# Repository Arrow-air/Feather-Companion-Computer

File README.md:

# Feather Flight Companion Computer

## Ground Control Station & Onboard Flight UI

### Functions:
1. Data Logger
2. Telemetry Server
3. User Interface Engine

## Table of Contents
1. [Introduction](#introduction)
2. [Architecture Overview](#architecture-overview)
3. [File Descriptions](#file-descriptions)
    - [FCPC.py](#fcpcpy)
    - [Data.py](#datapy)
    - [Veronte.py](#verontepy)
    - [BMS.py](#bmspy)
    - [VESCCAN.py](#vesccanpy)
    - [ESC.py](#escpy)
    - [CyphalCAN3.py](#cyphalcan3py)
    - [TCP.py](#tcppy)
    - [server.py](#serverpy)
    - [protocols_functions.py](#protocols_functionspy)
    - [display1.py](#display1py)
    - [display2.py](#display2py)
    - [Joystick.py](#joystickpy)
    - [LoRa.py](#lorapy)
    - [IO.py](#iopy)

## Introduction

The Flight Companion Computer system designed for both Ground Control Station (GCS) and onboard flight use (FUI). It integrates multiple functionalities including data logging, telemetry server, and a user interface engine. The system is modular, allowing for easy expansion and maintenance, and is designed to provide a robust Data interface for flight operations.

## Architecture Overview

The system is structured into multiple modules, each handling a specific aspect of the overall functionality. These modules include communication protocols, data handling, user interfaces, and specific hardware controls. The main control program loop resides in the `FCPC.py` file.

## File Descriptions

### FCPC.py
**Main Function and Control Logic**  
The central script that coordinates the activities of all other modules. Handles high-level decision making and ensures smooth operation of the entire system.

### Data.py
**Data Handling Module**  
Manages data storage and retrieval within the system. Provides functions for logging data, managing data formats, packaging data to be sent as telemetry.

### Veronte.py
**Veronte Module**  
Interfaces with the main Flight Controller, the Embention Veronte X1, over UART serial. packages flight sensor data, such as attitude and altitude etc.

### BMS.py
**Battery Management System (BMS) Module**  
Packages data from each of the 6 Ennoid X-LITE-V4 BMSs on board the aircraft, including voltage, current, temperature, and state of charge, etc.

### VESCCAN.py
**VESC-CAN Module**  
Interfaces with the VESC CAN bus protocol for interacting with data emminating from the Ennoid X-LITE-V4 BMSs, as implemented by Ennoid.

### ESC.py
**Electronic Speed Controller (ESC) Module**  
Packages data from each of the 6 Mad Motors ECSs on board the aircraft, including voltage, current, temperature, and state of charge, etc.

### CyphalCAN3.py
**Cyphal-CAN Protocol Module**  
Interfaces with the Cyphal-CAN CAN bus protocol for interacting with data emminating from the MAD Motors ECS, as implemented by MAD Motors.

### TCP.py
**TCP/IP Communication Module**  
Implements communication over TCP/IP, handling socket connections, data transmission, and reception over local network, send telemetry data to the displays.

### server.py
**Server Module**  
Sets up a network connection to `display1.py` and `display2.py` to send telementry data to the display screens

### protocols_functions.py
**Protocols Utility Functions Module**  
Contains utility functions used by `server.py`, `display1.py`, and `display2.py`. Provides common functionalities such as message parsing, checksum calculation, and other specific operations.

### display1.py
**Display Module 1**  
Responsible for rendering the "System State Window", primarily displaying data from the Flight Controller.

### display2.py
**Display Module 2**  
Responsible for rendering the "System Infromation Window", primarily displaying data from all the ESCs and BMSs.

### Joystick.py
**Joystick Input Module**  
Handles input from but Logitec USB and Otto CAN joystick devices. Reads joystick movements and button presses, translating their commands to the control system.

### LoRa.py
**Long Range Radio Communication Module**  
Implements communication over the LoRa protocol for long-range, low-power wireless communication. Handles message encoding, decoding, and transmission.

### IO.py
**Input-Output Module**  
Manages I/O on the RPI GPIO pins.

---

This README provides a comprehensive overview of the Project Feather system and its components. For detailed usage and additional information, refer to the documentation within each module and the main `FCPC.py` script, as well as the following reference documents:

## FCPC Concept Document 

[FCPC Concept]( https://docs.google.com/document/d/15r7cTYvV1hOLt8er7vyQtWU0twEOfAIIOQ0pdE-wRtA/edit?pli=1#heading=h.xr0raokzut1w )

## Project Feather Data Network & Ground Equipment Document

[Data Network & Ground Equipment]( https://docs.google.com/document/d/11VlSYsE245VFLZsYB7TvqWuuJ1UnPRjPKnnLWUzqcEM/edit )

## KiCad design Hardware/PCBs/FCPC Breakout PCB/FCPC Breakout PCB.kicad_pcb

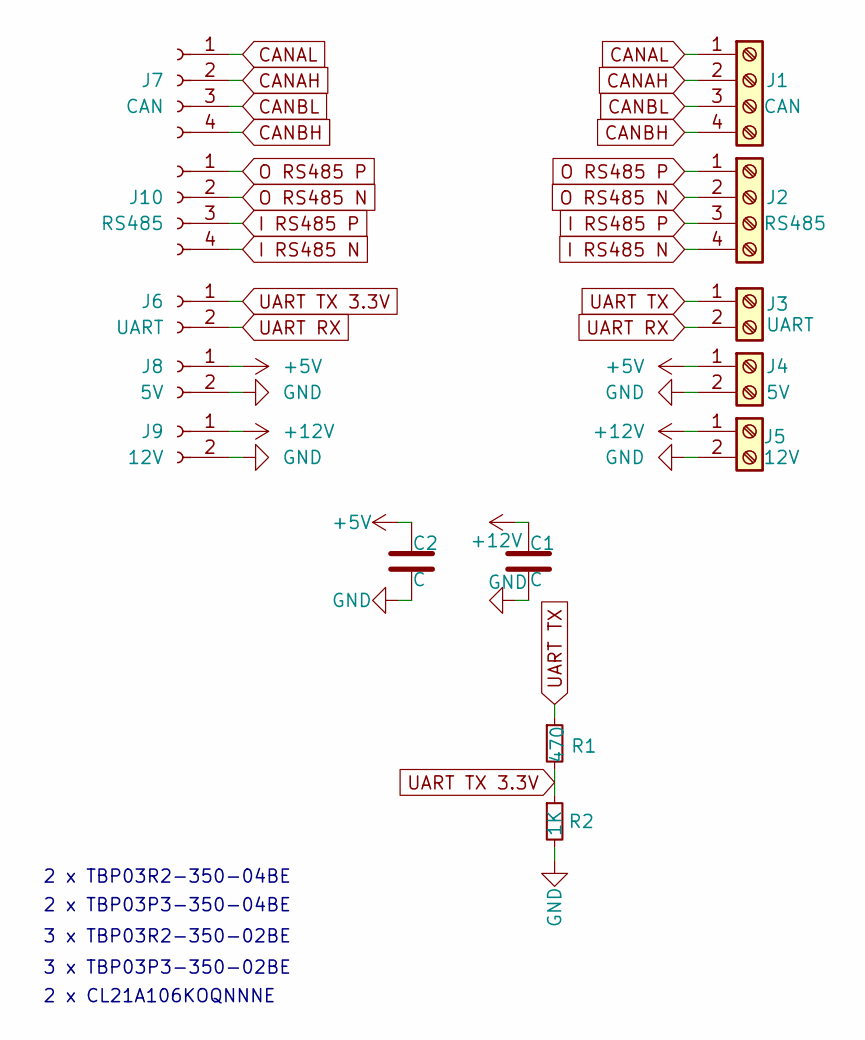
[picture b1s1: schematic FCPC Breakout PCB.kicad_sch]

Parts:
C1, C2: C; C_0805_2012Metric_Pad1.18x1.45mm_HandSolder
J1: CAN; PhoenixContact_MCV_1,5_4-G-3.5_1x04_P3.50mm_Vertical
J2: RS485; PhoenixContact_MCV_1,5_4-G-3.5_1x04_P3.50mm_Vertical
J3: UART; PhoenixContact_MCV_1,5_2-G-3.5_1x02_P3.50mm_Vertical
J4: 5V; PhoenixContact_MCV_1,5_2-G-3.5_1x02_P3.50mm_Vertical
J5: 12V; PhoenixContact_MCV_1,5_2-G-3.5_1x02_P3.50mm_Vertical
J6: UART; PinHeader_1x02_P2.54mm_Vertical
J7: CAN; PinHeader_1x04_P2.54mm_Vertical
J8: 5V; PinHeader_1x02_P2.54mm_Vertical
J9: 12V; PinHeader_1x02_P2.54mm_Vertical
J10: RS485; PinHeader_1x04_P2.54mm_Vertical
R1: 470; R_0805_2012Metric_Pad1.20x1.40mm_HandSolder
R2: 1K; R_0805_2012Metric_Pad1.20x1.40mm_HandSolder

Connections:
+5V: C2.1, J4.1, J8.1
+12V: C1.1, J5.1, J9.1
CANAH: J1.2, J7.2
CANAL: J1.1, J7.1
CANBH: J1.4, J7.4
CANBL: J1.3, J7.3
GND: C1.2, C2.2, J4.2, J5.2, J8.2, J9.2, R2.2
I RS485 N: J2.4, J10.4
I RS485 P: J2.3, J10.3
O RS485 N: J2.2, J10.2
O RS485 P: J2.1, J10.1
UART RX: J3.2, J6.2
UART TX: J3.1, R1.1
UART TX 3.3V: J6.1, R1.2, R2.1

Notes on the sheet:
2 x TBP03R2-350-04BE
2 x CL21A106KOQNNNE
3 x TBP03P3-350-02BE
2 x TBP03P3-350-04BE
3 x TBP03R2-350-02BE

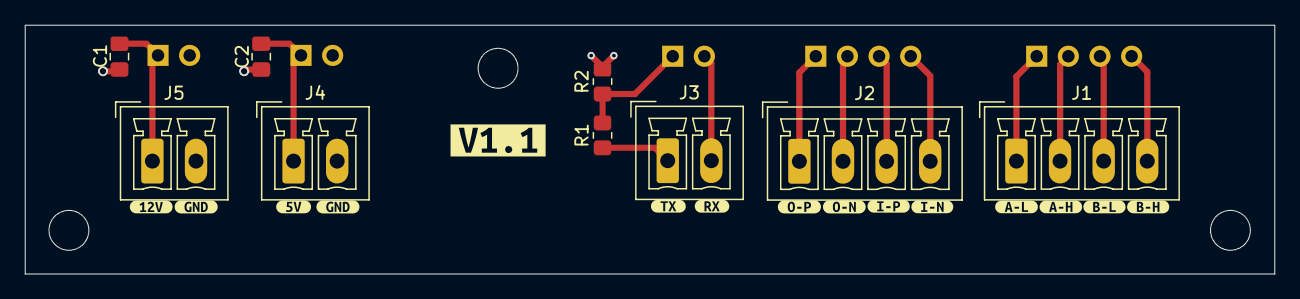
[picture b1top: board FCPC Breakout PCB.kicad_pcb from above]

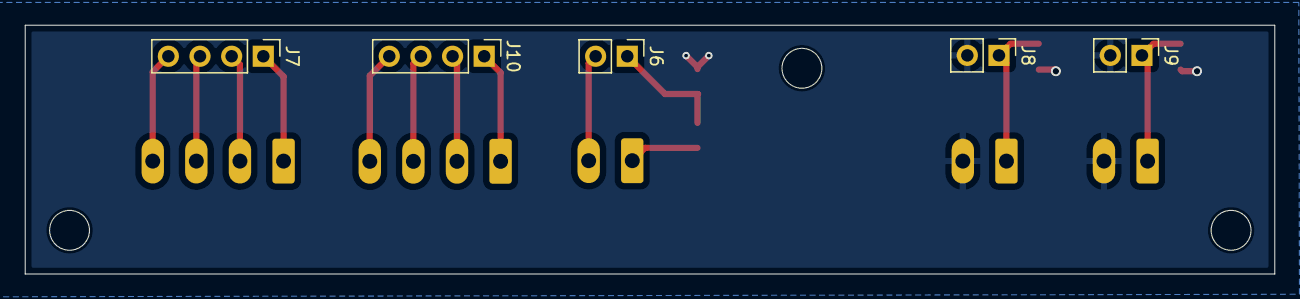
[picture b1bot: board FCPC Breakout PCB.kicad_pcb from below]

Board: 2 copper layers, 100.3 x 20.0 mm, 29 parts (5 on the bottom side), 14 nets.

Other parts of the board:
kibuzzard-66AD0A40: G***; kibuzzard-66AD0A40
kibuzzard-66AD0A64: G***; kibuzzard-66AD0A64
kibuzzard-6696DEDD, kibuzzard-6696DEDD#2: G***; kibuzzard-6696DEDD
kibuzzard-6696DEF0: G***; kibuzzard-6696DEF0
kibuzzard-6696DF0D: G***; kibuzzard-6696DF0D
kibuzzard-6696DF6D: G***; kibuzzard-6696DF6D
kibuzzard-6696DF63: G***; kibuzzard-6696DF63
kibuzzard-6696DFAD: G***; kibuzzard-6696DFAD
kibuzzard-6696DFC0: G***; kibuzzard-6696DFC0
kibuzzard-6696DFD9: G***; kibuzzard-6696DFD9
kibuzzard-6696E01E: G***; kibuzzard-6696E01E
kibuzzard-6696E02F: G***; kibuzzard-6696E02F
kibuzzard-6696E03F: G***; kibuzzard-6696E03F
kibuzzard-6696E054: G***; kibuzzard-6696E054

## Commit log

2024-05-30 Move over from Avionics System Repo
2024-05-31 veronte duummy working
2024-05-31 main
2024-06-22 redone ui mechanism
2024-06-22 update IO and server.py integration
2024-07-15 remodel
2024-07-16 hardware
2024-07-20 Enclosure
2024-08-02 FPCP Breakout PCB Update:
    B - L to B - H on error fix on silk screen
    V 1.1 Board created
2024-08-05 single motor test
    CyphalCAN3 modified to read single motor data for test
    (RPM calculation added = 3 * ES)
2024-08-06 update CyphalCAN
    CAN ID read Update
2024-08-08 PCB Update
    UART Voltage Divider 5V -> 3.3V
2024-08-17 Update
    Complete ESC & BMS Log dumpout to csv file
    ESC.py CAN ID update
    Test on CyphalCAN3 added
2024-08-17 update
    log file .csv opens in log directory
2024-08-18 Update
    Enclosure made taller for easier wiring
2024-08-24 accomodations
2024-08-25 test update
2024-08-25 throttle read update
2024-09-01 update enclosure
2024-09-15 LogParser
2024-09-17 LogParserApp
2024-09-25 New Veronte Config up
2024-10-14 update to BMS variable count 28 vs 27
2024-10-15 esc read update
2024-10-15 update print
2024-10-15 parsing update veronte
